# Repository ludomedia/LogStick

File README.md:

LogStick
========

Temperature and Humidity Logger emulating a Usb KeyBoard to output the results

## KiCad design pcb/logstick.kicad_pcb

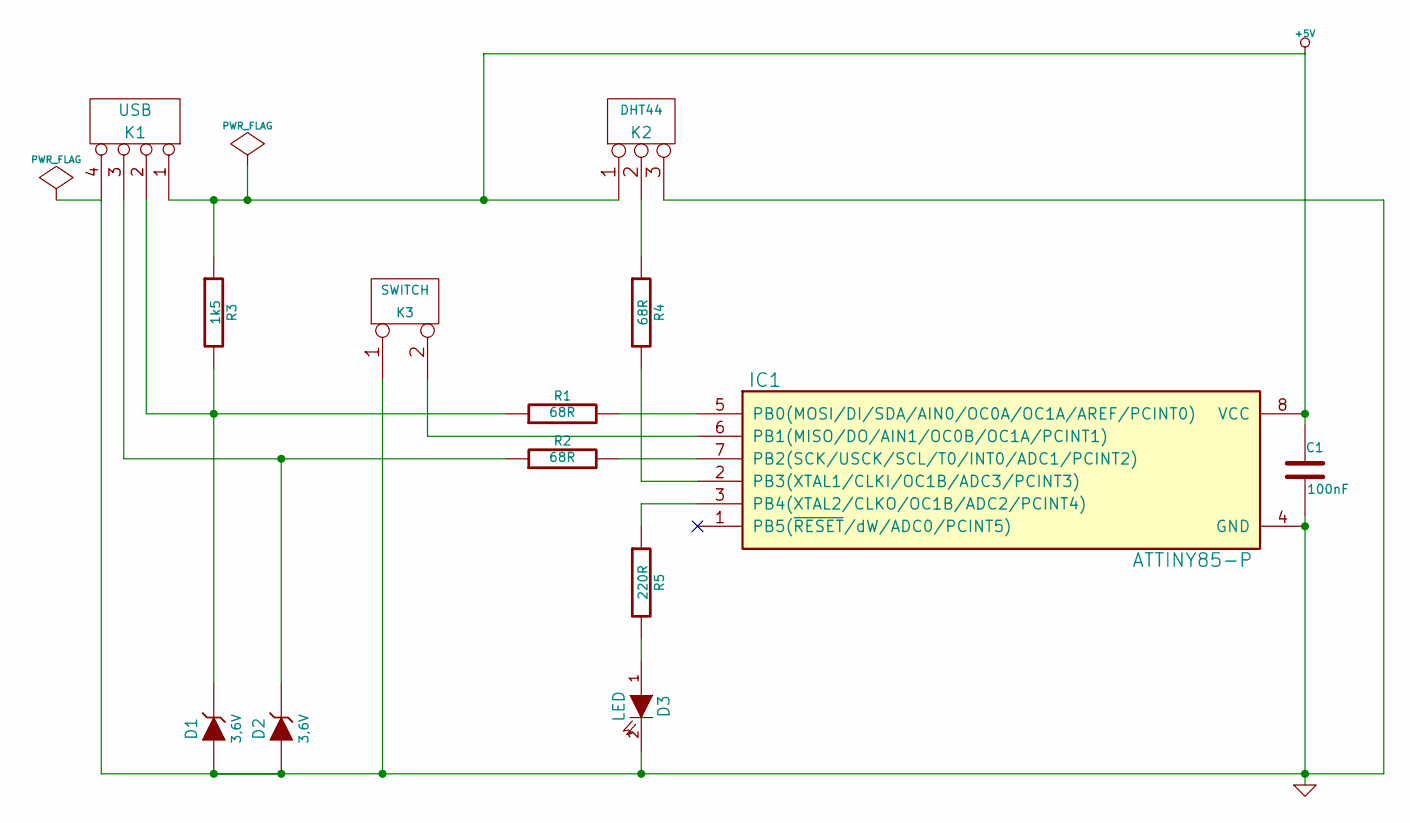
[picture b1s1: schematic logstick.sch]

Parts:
C1: 100nF
D1, D2: 3,6V
D3: LED
IC1: ATTINY85-P; DIP8
K1: USB
K2: DHT44
K3: SWITCH
R1, R2, R4: 68R
R3: 1k5
R5: 220R

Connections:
+5V: C1.1, IC1.8 (VCC), K1.1, K2.1, R3.1
GND: C1.2, D1.1 (A), D2.1 (A), D3.2 (K), IC1.4 (GND), K1.4, K2.3, K3.1
unnamed: IC1.3 (PB4(XTAL2/CLKO/OC1B/ADC2/PCINT4)), R5.1
unnamed: IC1.6 (PB1(MISO/DO/AIN1/OC0B/OC1A/PCINT1)), K3.2 (PM)
unnamed: D3.1 (A), R5.2
unnamed: IC1.2 (PB3(XTAL1/CLKI/OC1B/ADC3/PCINT3)), R4.2
unnamed: K2.2 (PM), R4.1
unnamed: D2.2 (K), K1.3, R2.1
unnamed: IC1.7 (PB2(SCK/USCK/SCL/T0/INT0/ADC1/PCINT2)), R2.2
unnamed: IC1.5 (PB0(MOSI/DI/SDA/AIN0/OC0A/OC1A/AREF/PCI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), R1.2
unnamed: D1.2 (K), K1.2, R1.1, R3.2

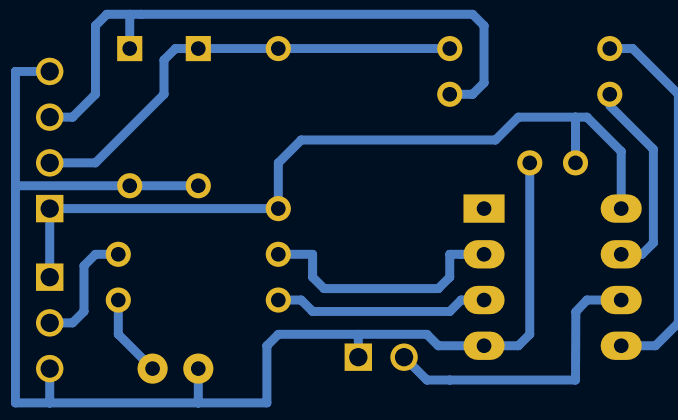
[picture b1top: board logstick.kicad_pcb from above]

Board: 2 copper layers, 13 parts (0 on the bottom side), 11 nets.

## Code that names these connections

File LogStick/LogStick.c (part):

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//#define DIGISPARK 1

#if defined(DIGISPARK)
#	define LED_PIN	PB1
#	define SWITCH_PIN PB0
#	define SENSOR_PIN PB2
#else
#	define LED_PIN	PB4
#	define SWITCH_PIN PB1
#	define SENSOR_PIN PB3
#endif


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
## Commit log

2013-05-15 initial version
2013-05-16 sensor test
2013-05-16 sensor reading
2013-05-17 eeprom log
2013-05-18 digispark defines
2013-06-09 3d box added
2013-06-13 correction R68
2013-06-17 autosave
2013-06-18 test
2013-08-25 released version 1.0

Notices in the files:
LogStick/LogStick.c:
License: GNU GPL v2
